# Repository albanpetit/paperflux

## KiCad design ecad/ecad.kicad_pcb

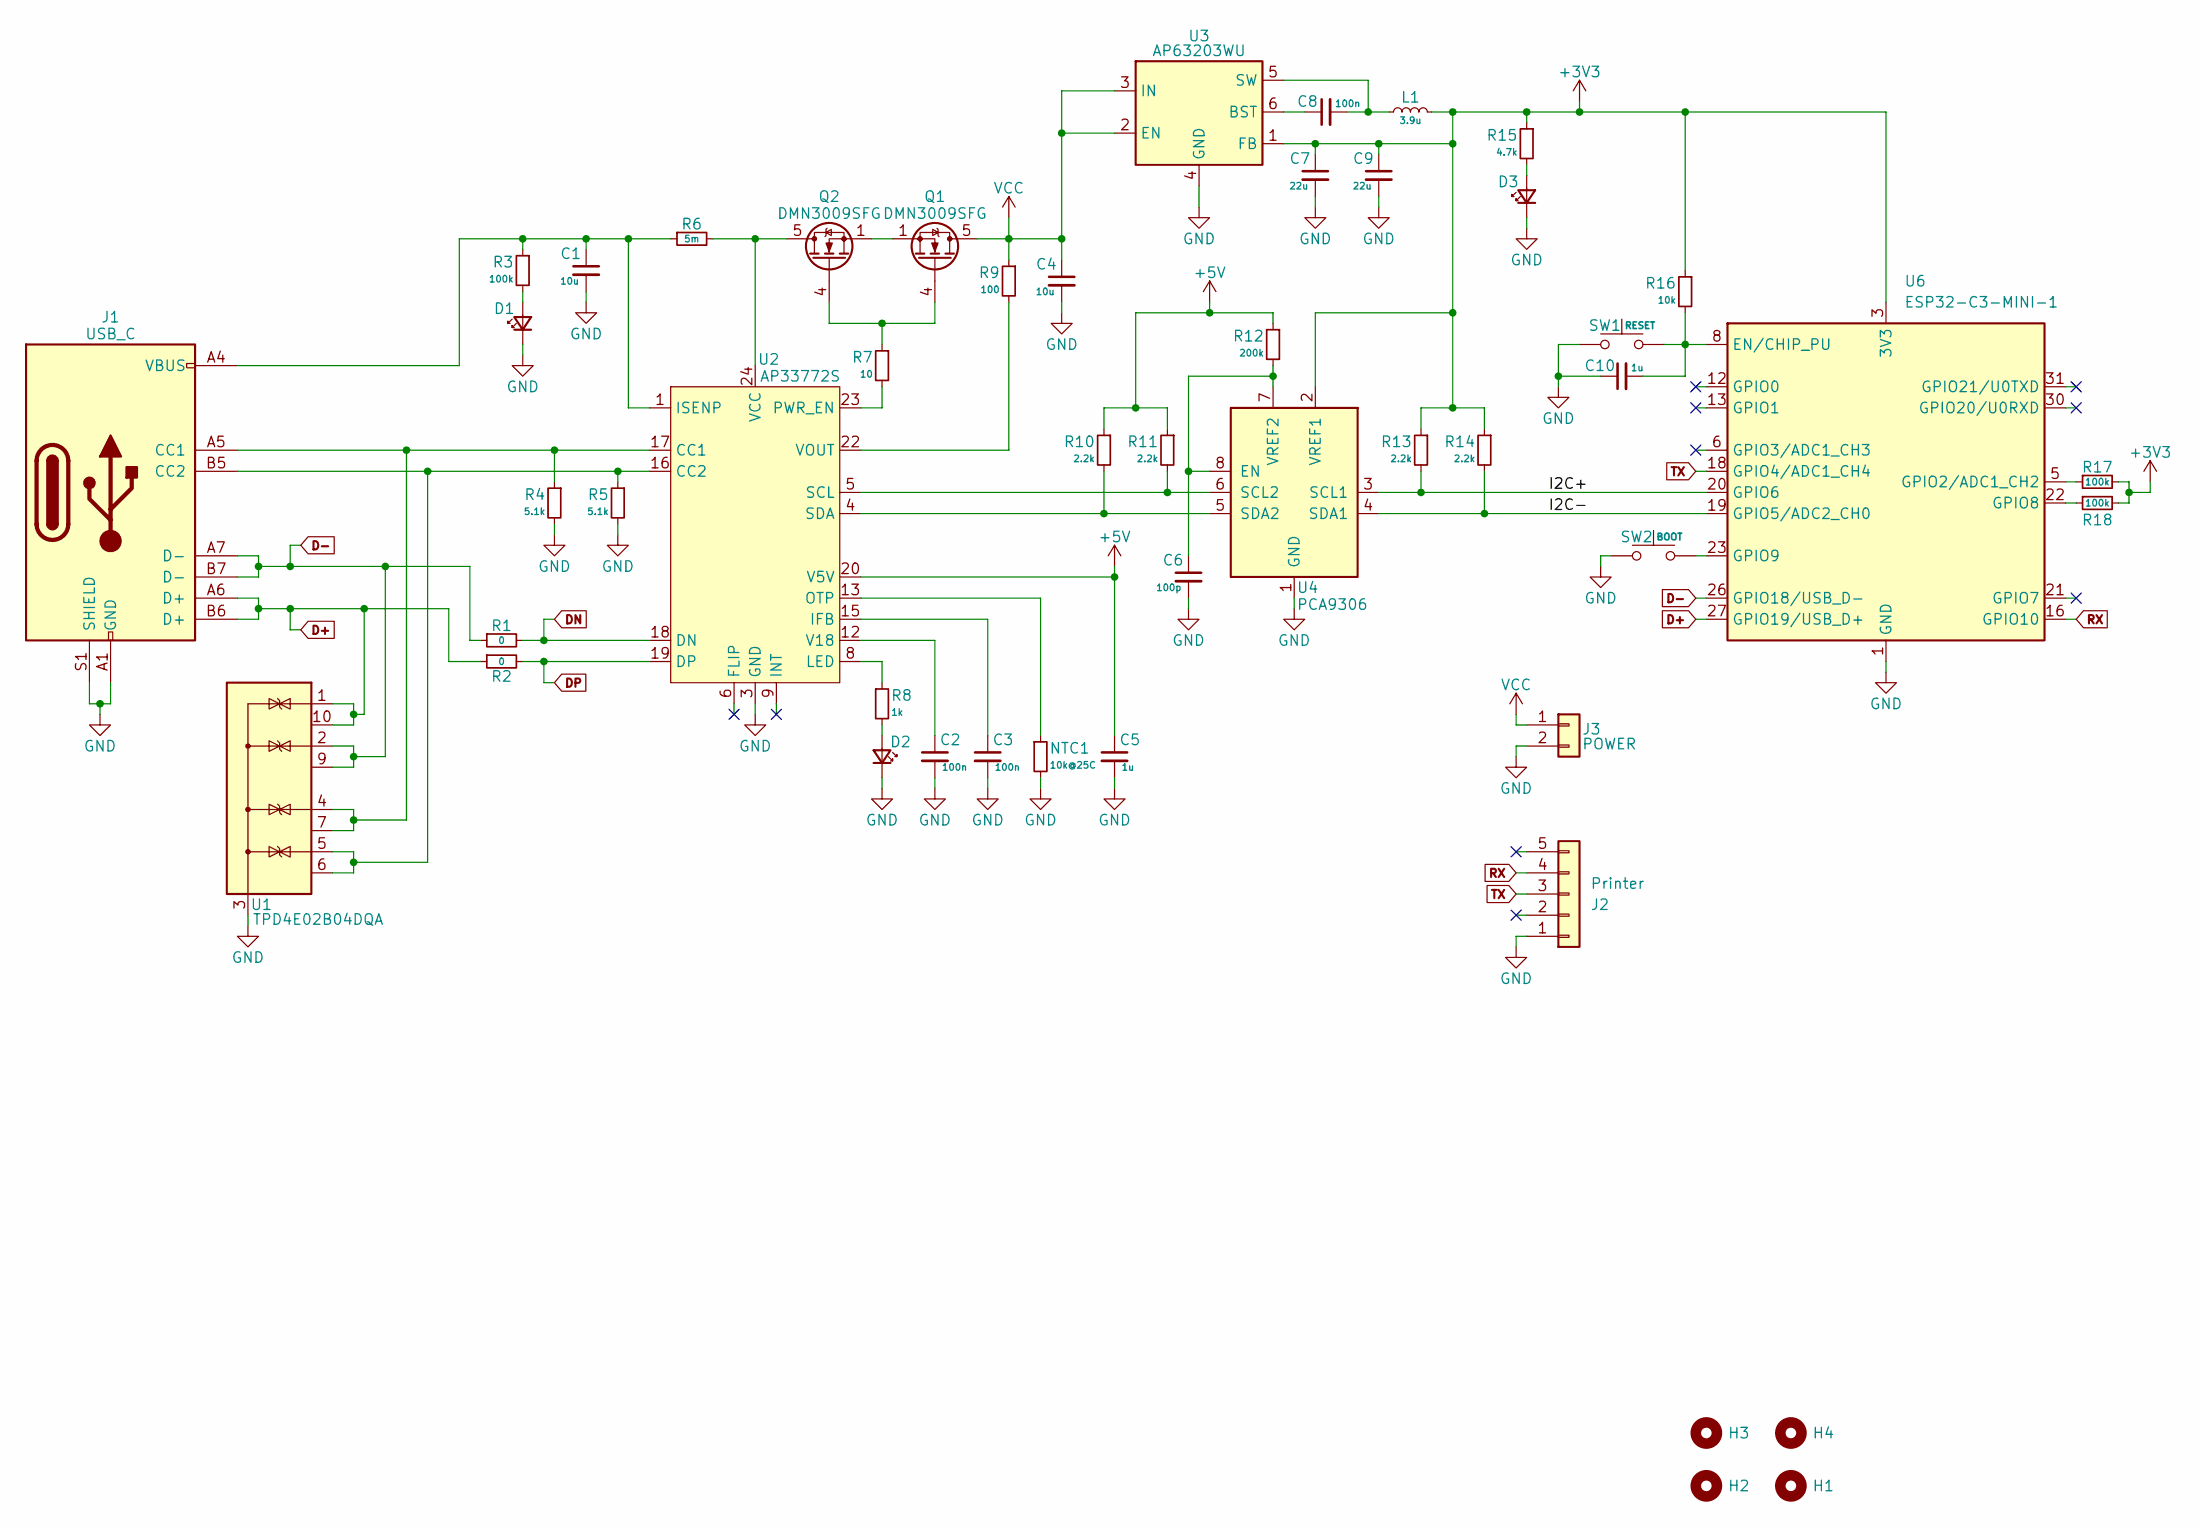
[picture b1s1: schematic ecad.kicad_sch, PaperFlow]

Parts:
C1, C4: 10u; C_0805_2012Metric
C2, C3, C8: 100n; C_0402_1005Metric
C5, C10: 1u; C_0402_1005Metric
C6: 100p; C_0402_1005Metric
C7, C9: 22u; C_0805_2012Metric
D1, D2, D3: LED_Small; LED_0402_1005Metric
H1, H2, H3, H4: MountingHole; MountingHole_2.2mm_M2_Pad_TopBottom
J1: USB_C; USB_C_Receptacle_JAE_DX07S016JA1R1500
J2: Printer; JST_PH_B5B-PH-K_1x05_P2.00mm_Vertical
J3: POWER; TerminalBlock_bornier-2_P5.08mm
L1: 3.9u; L_Wuerth_MAPI-3015
NTC1: 10k@25C; R_0402_1005Metric
Q1, Q2: DMN3009SFG; Diodes_PowerDI3333-8
R1, R2: 0; R_0402_1005Metric
R3, R17, R18: 100k; R_0402_1005Metric
R4, R5: 5.1k; R_0402_1005Metric
R6: 5m; R_1206_3216Metric
R7: 10; R_0402_1005Metric
R8: 1k; R_0402_1005Metric
R9: 100; R_0402_1005Metric
R10, R11, R13, R14: 2.2k; R_0402_1005Metric
R12: 200k; R_0402_1005Metric
R15: 4.7k; R_0402_1005Metric
R16: 10k; R_0402_1005Metric
SW1: RESET; SW_Push_1P1T_NO_CK_KMR2
SW2: BOOT; SW_Push_1P1T_NO_CK_KMR2
U1: TPD4E02B04DQA; USON-10_2.5x1.0mm_P0.5mm
U2: AP33772S; WQFN-24-1EP_4x4mm_P0.5mm_EP2.6x2.6mm_ThermalVias
U3: AP63203WU; TSOT-23-6
U4: PCA9306; TSSOP-8_3x3mm_P0.65mm
U6: ESP32-C3-MINI-1

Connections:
+3V3: C7.1, C9.1, L1.2, R13.1, R14.1, R15.1, R16.1, R17.2, R18.2, U3.1 (FB), U4.2 (VREF1), U6.3 (3V3)
+5V: C5.1, R10.1, R11.1, R12.1, U2.20 (V5V)
/I2C+: R13.2, U4.3 (SCL1), U6.20 (GPIO6)
/I2C-: R14.2, U4.4 (SDA1), U6.19 (GPIO5/ADC2_CH0)
D+: J1.A6 (D+), J1.B6 (D+), R2.1, U1.1 (IO1), U1.10 (NC), U6.27 (GPIO19/USB_D+)
D-: J1.A7 (D-), J1.B7 (D-), R1.1, U1.2 (IO2), U1.9 (NC), U6.26 (GPIO18/USB_D-)
DN: R1.2, U2.18 (DN)
DP: R2.2, U2.19 (DP)
GND: C1.2, C2.2, C3.2, C4.2, C5.2, C6.2, C7.2, C9.2, C10.1, D1.1 (K), D2.1 (K), D3.1 (K), J1.A1 (GND), J1.A12 (GND), J1.B1 (GND), J1.B12 (GND), J1.S1 (SHIELD), J2.1, J3.2, NTC1.2, R4.2, R5.2, SW1.1, SW2.1, U1.3 (G), U1.8 (G), U2.3 (GND), U2.25 (GND), U3.4 (GND), U4.1 (GND), U6.1 (GND), U6.2 (GND), U6.11 (GND), U6.14 (GND), U6.36 (GND), U6.37 (GND), U6.38 (GND), U6.39 (GND), U6.40 (GND), U6.41 (GND), U6.42 (GND), U6.43 (GND), U6.44 (GND), U6.45 (GND), U6.46 (GND), U6.47 (GND), U6.48 (GND), U6.49 (GND), U6.50 (GND), U6.51 (GND), U6.52 (GND), U6.53 (GND)
unnamed: D1.2 (A), R3.2
unnamed: D2.2 (A), R8.2
unnamed: D3.2 (A), R15.2
unnamed: J1.A5 (CC1), R4.1, U1.4 (IO3), U1.7 (NC), U2.17 (CC1)
unnamed: J1.B5 (CC2), R5.1, U1.5 (IO4), U1.6 (NC), U2.16 (CC2)
unnamed: Q1.4 (G), Q2.4 (G), R7.1
unnamed: Q1.1 (S), Q1.2 (S), Q1.3 (S), Q2.1 (S), Q2.2 (S), Q2.3 (S)
unnamed: Q2.5 (D), R6.2, U2.24 (VCC)
unnamed: C3.1, U2.15 (IFB)
unnamed: C1.1, J1.A4 (VBUS), J1.A9 (VBUS), J1.B4 (VBUS), J1.B9 (VBUS), R3.1, R6.1, U2.1 (ISENP)
unnamed: R8.1, U2.8 (LED)
unnamed: NTC1.1, U2.13 (OTP)
unnamed: R7.2, U2.23 (PWR_EN)
unnamed: R11.2, U2.5 (SCL), U4.6 (SCL2)
unnamed: R10.2, U2.4 (SDA), U4.5 (SDA2)
unnamed: C2.1, U2.12 (V18)
unnamed: R9.2, U2.22 (VOUT)
unnamed: C8.1, U3.6 (BST)
unnamed: C8.2, L1.1, U3.5 (SW)
unnamed: C6.1, R12.2, U4.7 (VREF2), U4.8 (EN)
unnamed: C10.2, R16.2, SW1.2, U6.8 (EN/CHIP_PU)
unnamed: R17.1, U6.5 (GPIO2/ADC1_CH2)
unnamed: R18.1, U6.22 (GPIO8)
unnamed: SW2.2, U6.23 (GPIO9)
RX: J2.4, U6.16 (GPIO10)
TX: J2.3, U6.18 (GPIO4/ADC1_CH4)
VCC: C4.1, J3.1, Q1.5 (D), R9.1, U3.2 (EN), U3.3 (IN)

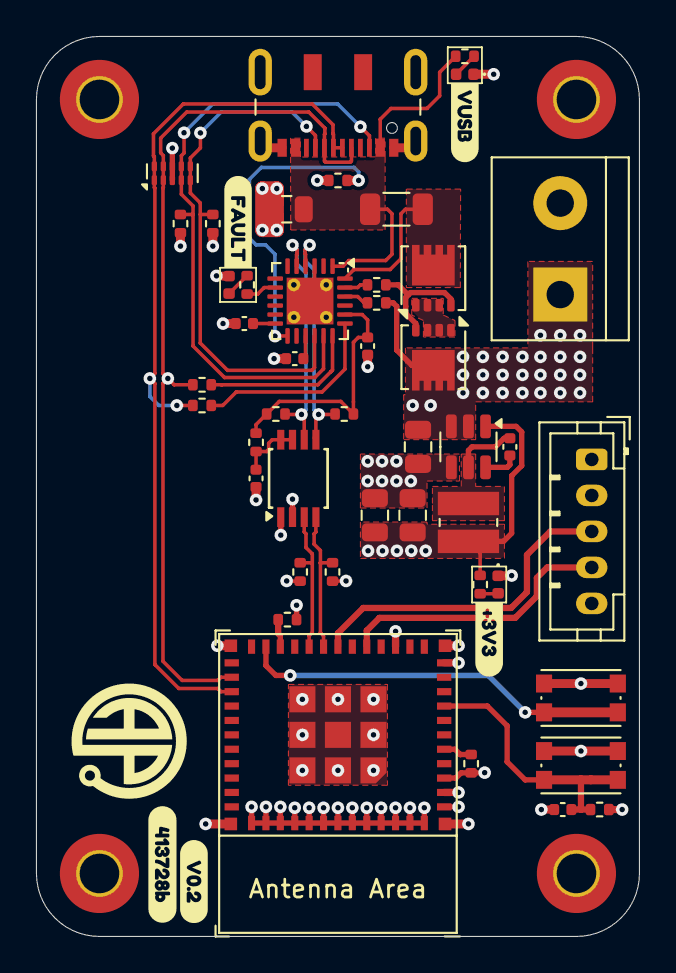
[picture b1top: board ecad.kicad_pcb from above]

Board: 4 copper layers, 33.5 x 50.0 mm, 54 parts (0 on the bottom side), 36 nets.

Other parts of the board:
kibuzzard-673BD329: G***; kibuzzard-673BD329
kibuzzard-673BD384: G***; kibuzzard-673BD384
kibuzzard-67439BF2: G***; kibuzzard-67439BF2
kibuzzard-68324C86: G***; kibuzzard-68324C86
kibuzzard-68324D05: G***; kibuzzard-68324D05

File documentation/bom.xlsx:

Bill of Materials
Reference | Value | Footprint | Datasheet | Qty | Mouser link
C1,C4 | 10u | Capacitor_SMD:C_0805_2012Metric | ~ | 2
C2,C3,C8,C10 | 100n | Capacitor_SMD:C_0402_1005Metric | ~ | 4
C5 | 1u | Capacitor_SMD:C_0402_1005Metric | ~ | 1
C6 | 100p | Capacitor_SMD:C_0402_1005Metric | ~ | 1
C7,C9 | 22u | Capacitor_SMD:C_0805_2012Metric | ~ | 2
D1,D2,D3 | LED_Small | LED_SMD:LED_0402_1005Metric | ~ | 3
J1 | USB_C | Connector_USB:USB_C_Receptacle_JAE_DX07S016JA1R1500 | https://www.usb.org/sites/default/files/documents/usb_type-c.zip | 1
J2 | Printer | Connector_JST:JST_PH_B5B-PH-K_1x05_P2.00mm_Vertical | ~ | 1
J3 | POWER | TerminalBlock:TerminalBlock_bornier-2_P5.08mm | ~ | 1
L1 | 3.9u | Inductor_SMD:L_Wuerth_MAPI-3015 | ~ | 1
NTC1 | 10k@25C | Resistor_SMD:R_0402_1005Metric | ~ | 1
Q1,Q2 | DMN3009SFG | Package_SON:Diodes_PowerDI3333-8 | https://www.diodes.com/assets/Datasheets/DMN3008SFG.pdf | 2
R1,R2 | 0 | Resistor_SMD:R_0402_1005Metric | ~ | 2
R3,R17,R18 | 100k | Resistor_SMD:R_0402_1005Metric | ~ | 3
R4,R5 | 5.1k | Resistor_SMD:R_0402_1005Metric | ~ | 2
R6 | 5m | Resistor_SMD:R_1206_3216Metric | ~ | 1
R7 | 10 | Resistor_SMD:R_0402_1005Metric | ~ | 1
R8 | 1k | Resistor_SMD:R_0402_1005Metric | ~ | 1
R9 | 100 | Resistor_SMD:R_0402_1005Metric | ~ | 1
R10,R11,R13,R14 | 2.2k | Resistor_SMD:R_0402_1005Metric | ~ | 4
R12 | 200k | Resistor_SMD:R_0402_1005Metric | ~ | 1
R15,R16 | 4.7k | Resistor_SMD:R_0402_1005Metric | ~ | 2
SW1 | RESET | Button_Switch_SMD:SW_Push_1P1T_NO_CK_KMR2 | ~ | 1
SW2 | BOOT | Button_Switch_SMD:SW_Push_1P1T_NO_CK_KMR2 | ~ | 1
U1 | TPD4E02B04DQA | Package_SON:USON-10_2.5x1.0mm_P0.5mm | http://www.ti.com/lit/ds/symlink/tpd4e02b04.pdf | 1
U2 | AP33772S | Package_DFN_QFN:WQFN-24-1EP_4x4mm_P0.5mm_EP2.6x2.6mm_ThermalVias |  | 1
U3 | AP63203WU | Package_TO_SOT_SMD:TSOT-23-6 | https://www.diodes.com/assets/Datasheets/AP63200-AP63201-AP6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 | 1
U4 | PCA9306 | Package_SO:TSSOP-8_3x3mm_P0.65mm | http://www.ti.com/lit/ds/symlink/pca9306.pdf | 1
U6 | ESP32-C3-MINI-1 | ESPRESSIF:ESP32-C3-MINI-1 | https://www.espressif.com/sites/default/files/documentation/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 | 1

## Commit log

2024-10-29 git: first commit
2024-11-03 docs: add some datasheets of selected components
2024-11-04 docs: add PCA9306 datasheet
2024-11-04 docs: add DMN3009SFG mosfet datasheet
2024-11-04 docs: add AP33772S dev kit datasheet
2024-11-05 docs: add AP3203 buck converter datasheet
2024-11-05 docs: add TPD4E05U06 ESD protection datasheet
2024-11-06 git: update gitignore with vscode and kicad specifications
2024-11-06 ecad: schematic first version before review
2024-11-07 docs: add datasheet USB4110 usb c connector
2024-11-15 docs: add datasheet WE-MAPI3015 buck converter inductor
2024-11-15 git: change gitignore to add gerber.zip files
2024-11-24 ecad: gerber folder, espressif lib and some pcb design
2024-11-25 ecad: 4 layers setup and more routing
2024-12-01 docs: esp32c3 design guide documentation
2025-05-08 git: update gitignore
2025-05-08 firmware fix: remove useless test code
2025-05-08 firmware feat: add some test code for printer
2025-05-21 docs: fix documentation files name
2025-05-21 docs: add general bom file, only ecad now
2025-05-21 ecad feat: welcome ibom
2025-05-21 firmware feat: add some thermal printer test code
2025-05-21 ecad fix: board placement and page template
2025-05-21 docs: change documentation file name
2025-05-24 ecad fix: fix bad connection to usb
2025-05-24 ecad: change ecad version to v0.2
2025-05-24 firmware fix: changer printer test to test usb pd
2025-05-25 ecad fix: change some reset res value according to datasheet
2025-05-25 docs: change folder structure
